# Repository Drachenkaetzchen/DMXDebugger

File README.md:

# DMX/RDM Adapter / RS485 Hub

This is a board which allows you to:
- Interconnect any standard DMX plugs, which includes XLR 3 pin male+female, XLR 5 pin male+female and RJ45
- Flip the data lines for each port in case of wiring error
- Connect each plug to an internal RS485 hub (in "direct" mode, each Data+/Data- lines are connected to each other)
- Terminate each port and enable/disable RX (only if port is connected to the RS485 hub)
- Connect a logic probe to the RS485 hub or to the secondary data ports (useful for the OLA logic sniffer)
- Display RX/TX status (RS485 hub mode only)
- Powered via battery (9V) or USB

# Applications

## Interconnect DMX plug formats directly

1. This mode works unpowered. You don't need to connect a battery or USB
2. Flip all switches from "TO HUB" to "DIRECT"
3. Connect exactly 2 plugs you wish to connect. If you connect more, data collisions can occur on the bus

## Interconnect DMX plug formats via the RS485 hub

1. This mode requires power. Connect a 9V battery or USB and flip the power switch to the specific "ON" position (either USB or BATTERY)
2. Flip the switches for all used ports from "DIRECT" to "HUB"
3. Connect as many plugs as you like
4. The LEDs should indicate RX/TX status

## Retrieve the data on the DMX bus via a logic analyzer

1. Set up as described in "Interconnect DMX plug formats via the RS485 hub"
2. Connect your logic probe to the GND and DATA pins on the bottom right

## Retrieve the data of the DMX secondary data lines

1. This mode works unpowered. However, you need an RS485 driver (like the SN75176) to convert the differential signal into logic levels
2. Connect your probe to the secondary data port

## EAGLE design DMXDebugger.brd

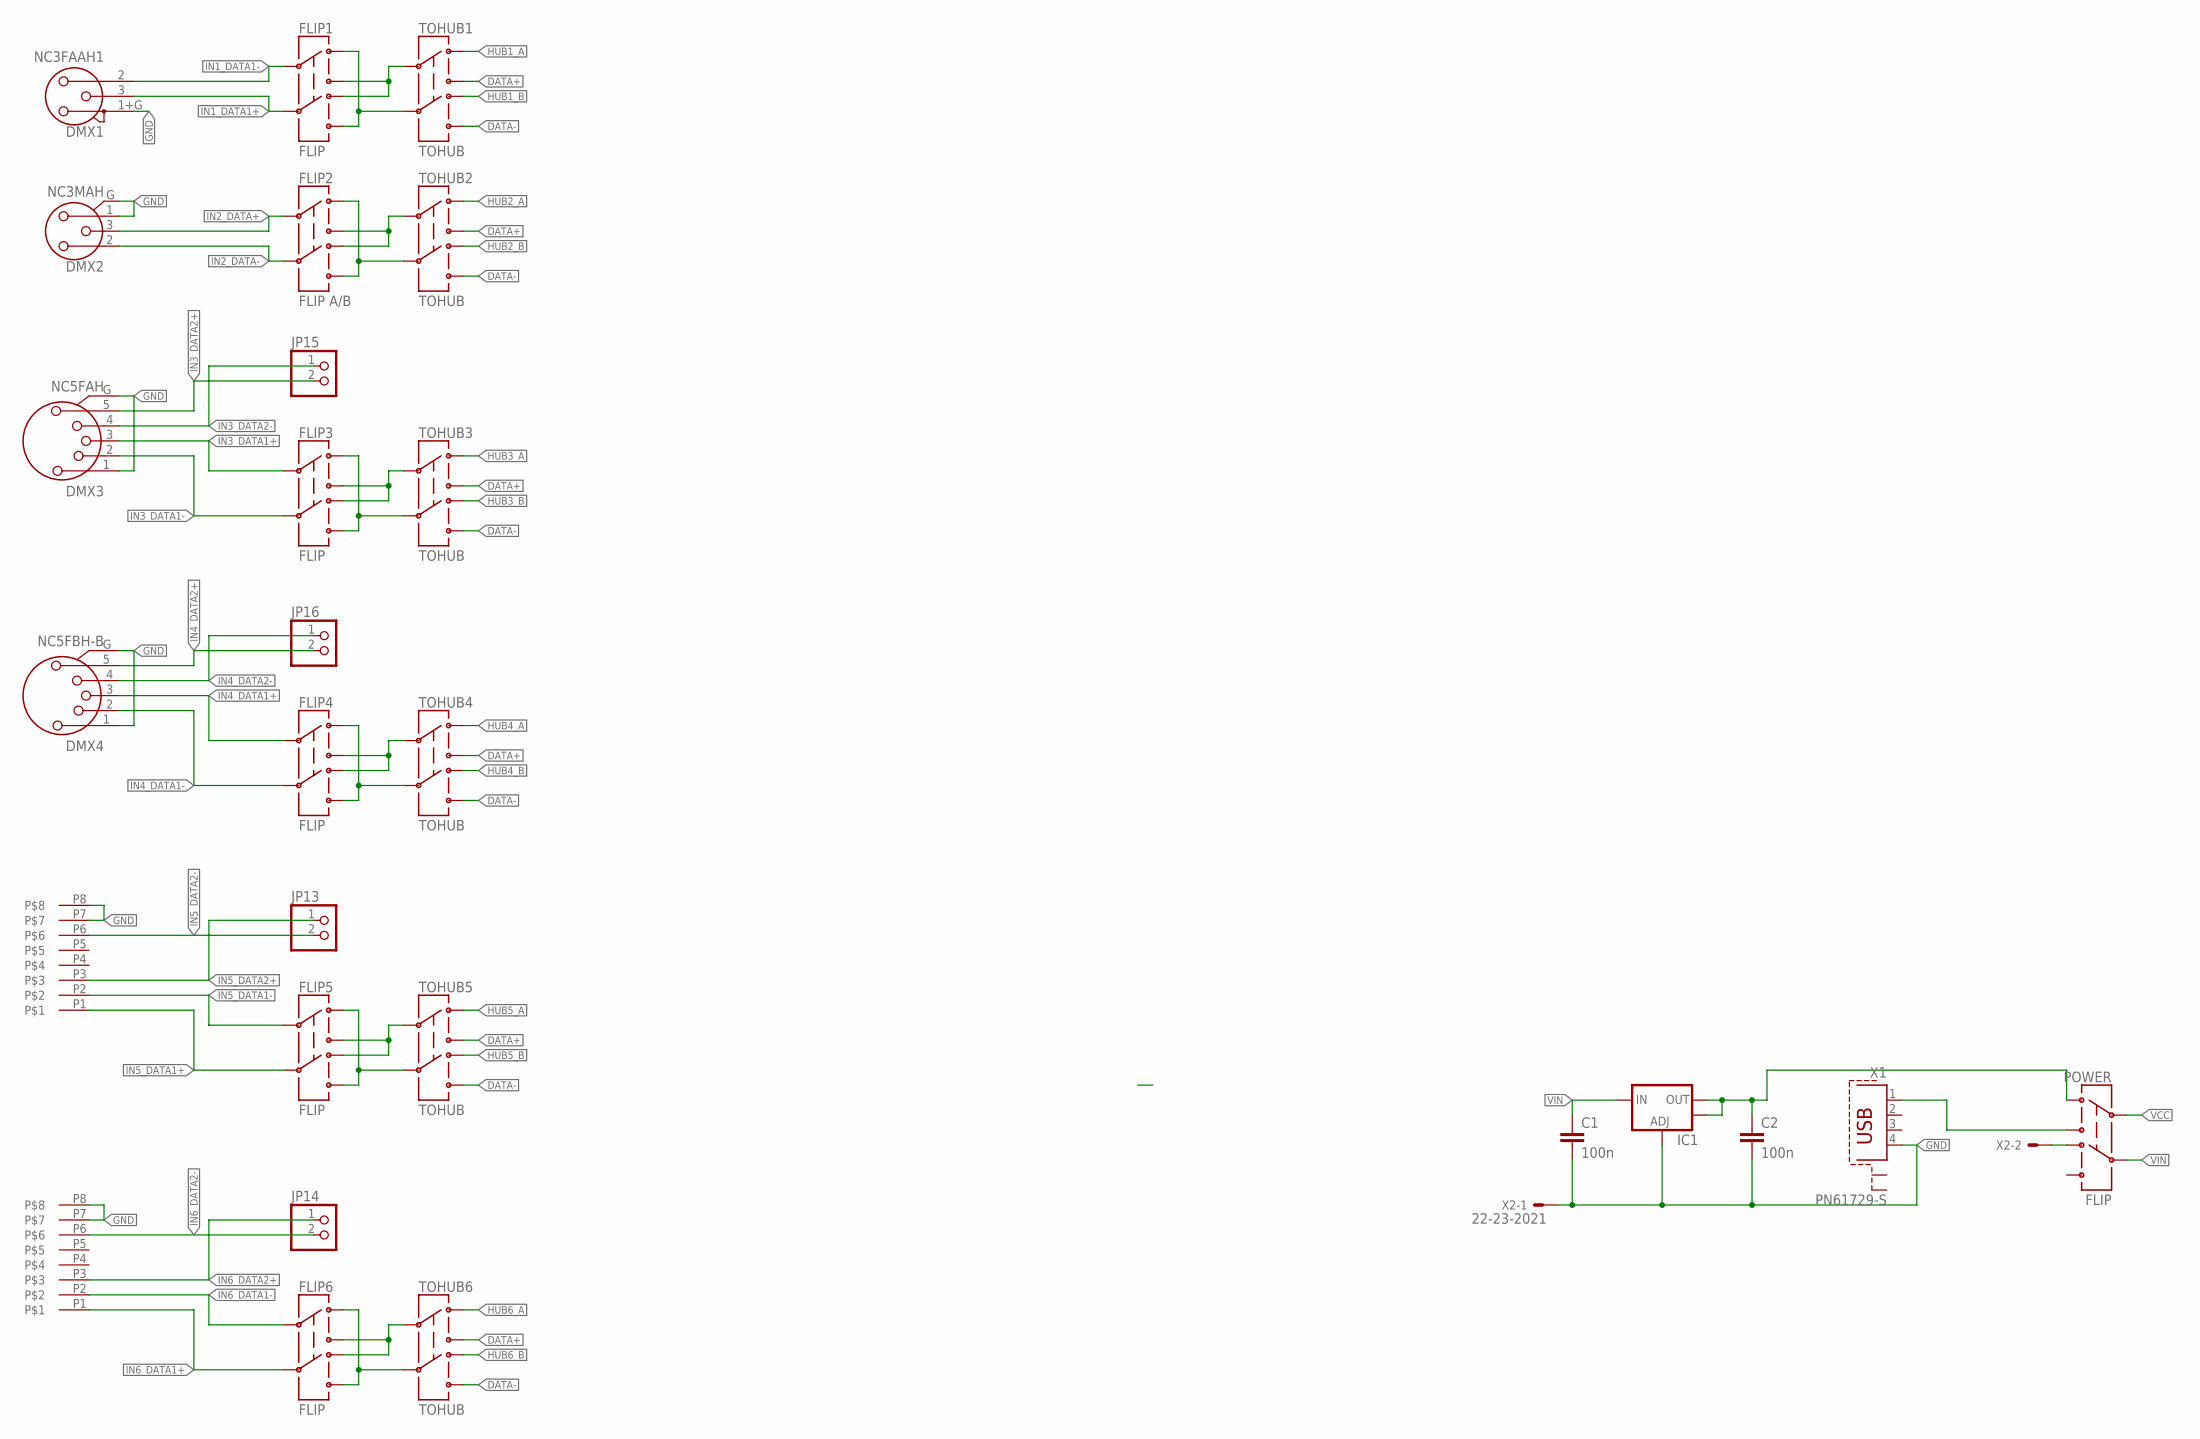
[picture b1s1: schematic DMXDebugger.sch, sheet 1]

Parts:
C1, C2: 100n; C1206
DMX1: NC3FAAH1; NC3FAH1
DMX2: NC3MAH; NC3FAH2
DMX3: NC5FAH
DMX4: NC5FBH-B
DMX5, DMX6: RJHS508; P-RJHS-538X
FLIP1, FLIP3, FLIP4, FLIP5, FLIP6: FLIP; MSS-2235
FLIP2: FLIP A/B; MSS-2235
IC1: V_REG_LM1117SOT223; SOT223
JP13, JP14, JP15, JP16: PINHD-1X2; 1X02
POWER: FLIP; MSS-2235
TOHUB1, TOHUB2, TOHUB3, TOHUB4, TOHUB5, TOHUB6: TOHUB; MSS-2235
X1: PN61729-S
X2: 22-23-2021

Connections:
DATA+: TOHUB1.3, TOHUB2.3, TOHUB3.3, TOHUB4.3, TOHUB5.3, TOHUB6.3
DATA-: TOHUB1.4 (6), TOHUB2.4 (6), TOHUB3.4 (6), TOHUB4.4 (6), TOHUB5.4 (6), TOHUB6.4 (6)
GND: C1.2, C2.2, DMX1.1+G (1), DMX2.1 (2), DMX2.G, DMX3.1, DMX3.G, DMX4.1, DMX4.G, DMX5.P7, DMX5.P8, DMX6.P7, DMX6.P8, IC1.1 (ADJ), X1.4, X2.1; also elsewhere on the board
HUB1_A: TOHUB1.1; also elsewhere on the board
HUB1_B: TOHUB1.6 (4); also elsewhere on the board
HUB2_A: TOHUB2.1; also elsewhere on the board
HUB2_B: TOHUB2.6 (4); also elsewhere on the board
HUB3_A: TOHUB3.1; also elsewhere on the board
HUB3_B: TOHUB3.6 (4); also elsewhere on the board
HUB4_A: TOHUB4.1; also elsewhere on the board
HUB4_B: TOHUB4.6 (4); also elsewhere on the board
HUB5_A: TOHUB5.1; also elsewhere on the board
HUB5_B: TOHUB5.6 (4); also elsewhere on the board
HUB6_A: TOHUB6.1; also elsewhere on the board
HUB6_B: TOHUB6.6 (4); also elsewhere on the board
IN1_DATA1+: DMX1.3, FLIP1.5
IN1_DATA1-: DMX1.2, FLIP1.2
IN2_DATA+: DMX2.3, FLIP2.2
IN2_DATA-: DMX2.2 (1), FLIP2.5
IN3_DATA1+: DMX3.3, FLIP3.2
IN3_DATA1-: DMX3.2, FLIP3.5
IN3_DATA2+: DMX3.5, JP15.2
IN3_DATA2-: DMX3.4, JP15.1
IN4_DATA1+: DMX4.3, FLIP4.2
IN4_DATA1-: DMX4.2, FLIP4.5
IN4_DATA2+: DMX4.5, JP16.2
IN4_DATA2-: DMX4.4, JP16.1
IN5_DATA1+: DMX5.P1, FLIP5.5
IN5_DATA1-: DMX5.P2, FLIP5.2
IN5_DATA2+: DMX5.P3, JP13.1
IN5_DATA2-: DMX5.P6, JP13.2
IN6_DATA1+: DMX6.P1, FLIP6.5
IN6_DATA1-: DMX6.P2, FLIP6.2
IN6_DATA2+: DMX6.P3, JP14.1
IN6_DATA2-: DMX6.P6, JP14.2
unnamed: POWER.6 (4), X2.2
unnamed: POWER.3, X1.1
unnamed: FLIP1.3, FLIP1.6 (4), TOHUB1.2
unnamed: FLIP1.1, FLIP1.4 (6), TOHUB1.5
unnamed: FLIP2.1, FLIP2.4 (6), TOHUB2.5
unnamed: FLIP2.3, FLIP2.6 (4), TOHUB2.2
unnamed: FLIP3.1, FLIP3.4 (6), TOHUB3.5
unnamed: FLIP4.1, FLIP4.4 (6), TOHUB4.5
unnamed: FLIP5.1, FLIP5.4 (6), TOHUB5.5
unnamed: FLIP3.3, FLIP3.6 (4), TOHUB3.2
unnamed: FLIP4.3, FLIP4.6 (4), TOHUB4.2
unnamed: FLIP5.3, FLIP5.6 (4), TOHUB5.2
unnamed: FLIP6.1, FLIP6.4 (6), TOHUB6.5
unnamed: FLIP6.3, FLIP6.6 (4), TOHUB6.2
VCC: POWER.2; also elsewhere on the board
VIN: C1.1, IC1.3 (IN), POWER.5
VOUT: C2.1, IC1.2 (OUT), IC1.4 (OUT), POWER.1

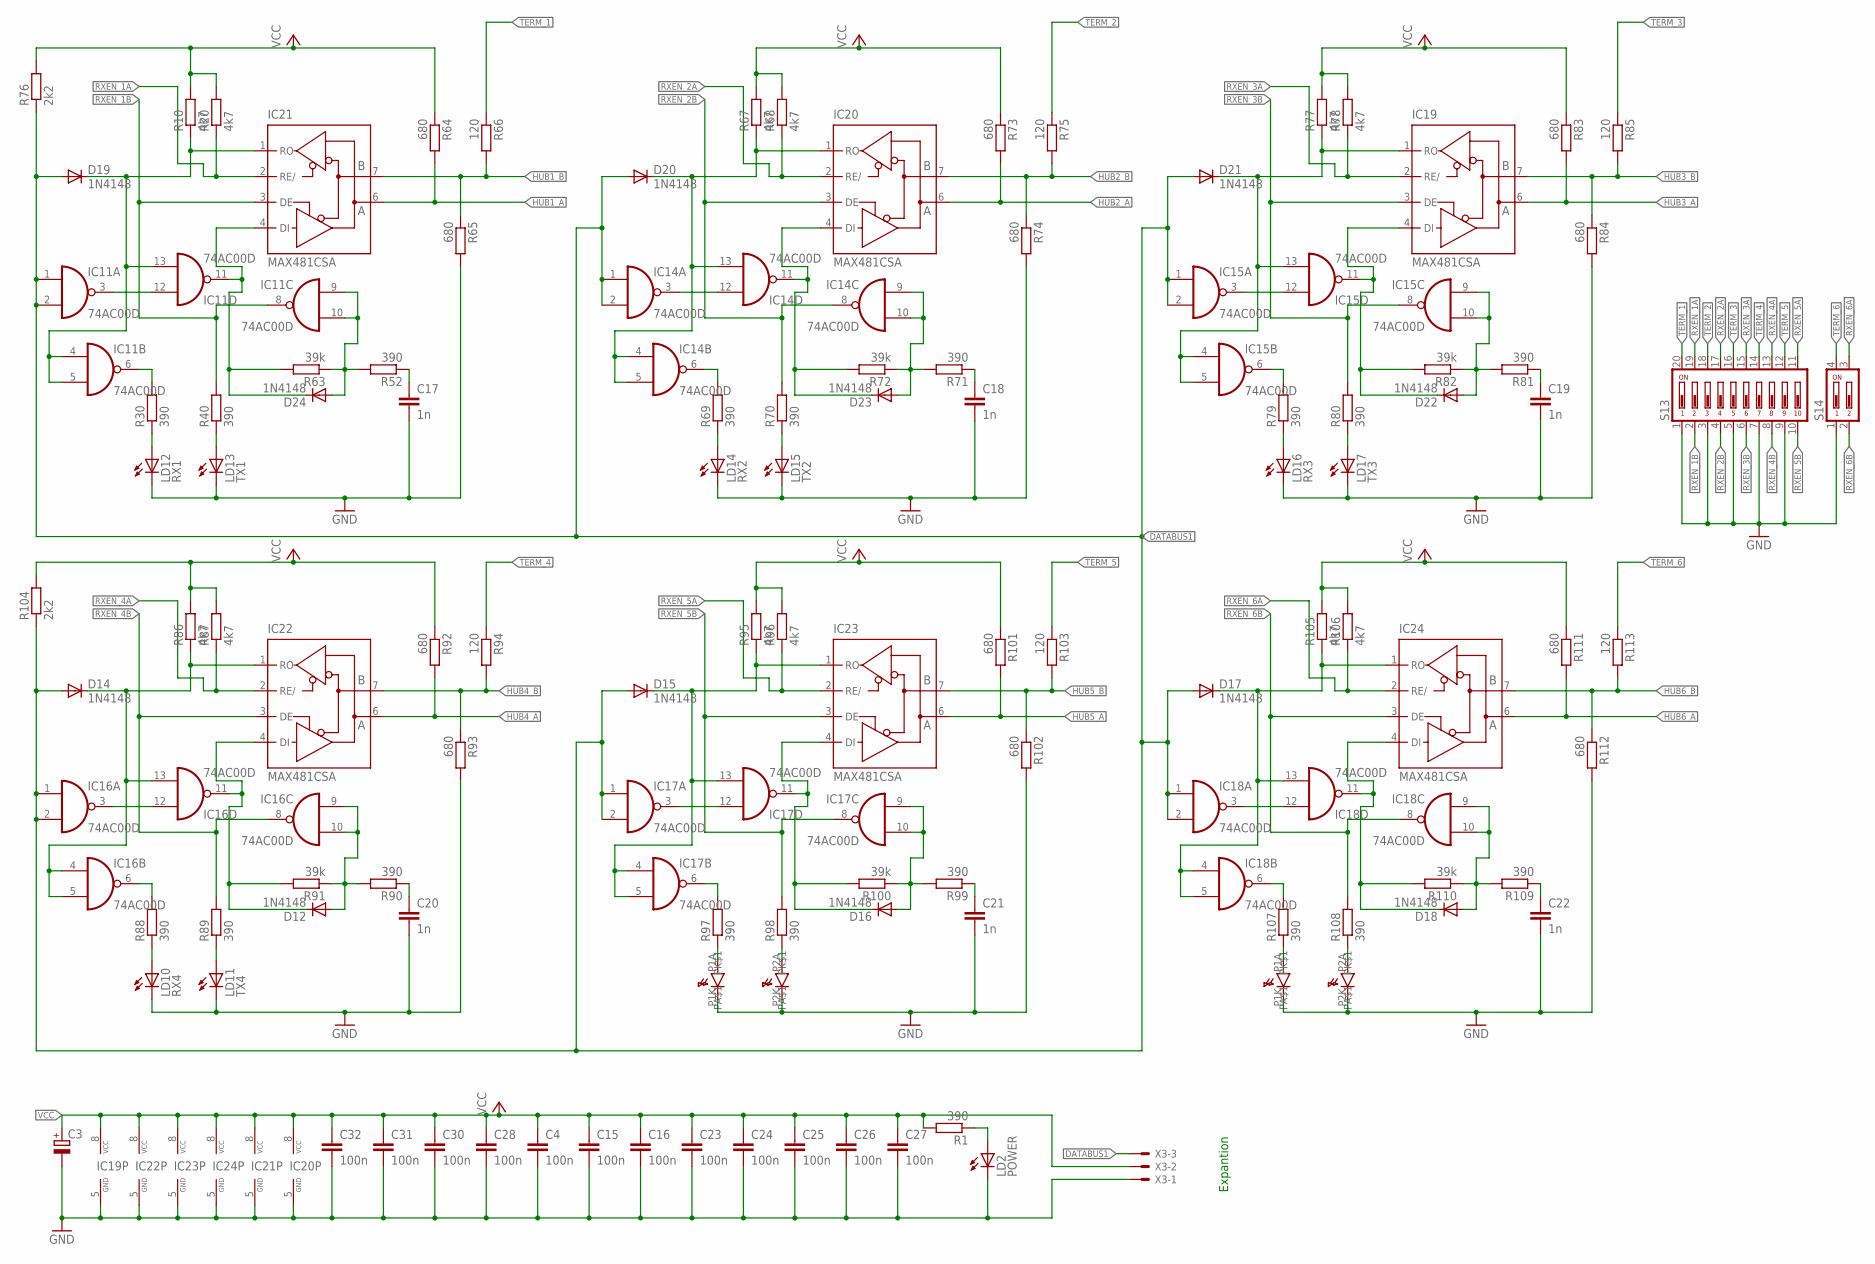
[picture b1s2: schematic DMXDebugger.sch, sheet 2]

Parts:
C3: CPOL-EUD; PANASONIC_D
C4, C15, C16, C23, C24, C25, C26, C27, C28, C30, C31, C32: 100n; C1206
C17, C18, C19, C20, C21, C22: 1n; C1206
D12, D14, D15, D16, D17, D18, D19, D20, D21, D22, D23, D24: 1N4148; MINIMELF
DMX5, DMX6: RJHS508; P-RJHS-538X
IC11, IC14, IC15, IC16, IC17, IC18: 74AC00D; SO14
IC19, IC20, IC21, IC22, IC23, IC24: MAX481CSA; SO08
LD2: POWER; CHIP-LED0603
LD10: RX4; CHIP-LED0603
LD11: TX4; CHIP-LED0603
LD12: RX1; CHIP-LED0603
LD13: TX1; CHIP-LED0603
LD14: RX2; CHIP-LED0603
LD15: TX2; CHIP-LED0603
LD16: RX3; CHIP-LED0603
LD17: TX3; CHIP-LED0603
R1, R30, R40, R52, R69, R70, R71, R79, R80, R81, R88, R89, R90, R97, R98, R99, R107, R108, R109: 390; R1206
R10, R20, R67, R68, R77, R78, R86, R87, R95, R96, R105, R106: 4k7; R1206
R63, R72, R82, R91, R100, R110: 39k; R1206
R64, R65, R73, R74, R83, R84, R92, R93, R101, R102, R111, R112: 680; R1206
R66, R75, R85, R94, R103, R113: 120; R1206
R76, R104: 2k2; R1206
S13: DIP10YL
S14: DIP02YL
X3: 22-23-2031

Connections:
DATABUS1: D14.A, D15.A, D17.A, D19.A, D20.A, D21.A, IC11.1 (I0), IC11.2 (I1), IC14.1 (I0), IC14.2 (I1), IC15.1 (I0), IC15.2 (I1), IC16.1 (I0), IC16.2 (I1), IC17.1 (I0), IC17.2 (I1), IC18.1 (I0), IC18.2 (I1), R76.1, R104.1, X3.3
GND: C3.-, C4.2, C15.2, C16.2, C17.2, C18.2, C19.2, C20.2, C21.2, C22.2, C23.2, C24.2, C25.2, C26.2, C27.2, C28.2, C30.2, C31.2, C32.2, DMX5.P1K (PK$1), DMX5.P2K (PK$1), DMX6.P1K (PK$1), DMX6.P2K (PK$1), IC11.7 (GND), IC14.7 (GND), IC15.7 (GND), IC16.7 (GND), IC17.7 (GND), IC18.7 (GND), IC19.5 (GND), IC20.5 (GND), IC21.5 (GND), IC22.5 (GND), IC23.5 (GND), IC24.5 (GND), LD2.C, LD10.C, LD11.C, LD12.C, LD13.C, LD14.C, LD15.C, LD16.C, LD17.C, R65.2, R74.2, R84.2, R93.2, R102.2, R112.2, S13.1, S13.3, S13.5, S13.7, S13.9, S14.1, X3.1; also elsewhere on the board
HUB1_A: IC21.6 (A), R64.2; also elsewhere on the board
HUB1_B: IC21.7 (B), R65.1, R66.2; also elsewhere on the board
HUB2_A: IC20.6 (A), R73.2; also elsewhere on the board
HUB2_B: IC20.7 (B), R74.1, R75.2; also elsewhere on the board
HUB3_A: IC19.6 (A), R83.2; also elsewhere on the board
HUB3_B: IC19.7 (B), R84.1, R85.2; also elsewhere on the board
HUB4_A: IC22.6 (A), R92.2; also elsewhere on the board
HUB4_B: IC22.7 (B), R93.1, R94.2; also elsewhere on the board
HUB5_A: IC23.6 (A), R101.2; also elsewhere on the board
HUB5_B: IC23.7 (B), R102.1, R103.2; also elsewhere on the board
HUB6_A: IC24.6 (A), R111.2; also elsewhere on the board
HUB6_B: IC24.7 (B), R112.1, R113.2; also elsewhere on the board
unnamed: LD2.A, R1.1
unnamed: LD13.A, R40.1
unnamed: LD12.A, R30.1
unnamed: D19.C, IC11.4 (I0), IC11.5 (I1), IC11.13 (I1), IC21.1 (RO), R10.1
unnamed: IC11.3 (O), IC11.12 (I0)
unnamed: IC11.6 (O), R30.2
unnamed: D24.A, IC11.9 (I0), IC11.10 (I1), R52.2, R63.1
unnamed: D24.C, IC11.11 (O), IC21.4 (DI), R63.2
unnamed: C17.1, R52.1
unnamed: LD15.A, R70.1
unnamed: LD14.A, R69.1
unnamed: D20.C, IC14.4 (I0), IC14.5 (I1), IC14.13 (I1), IC20.1 (RO), R67.1
unnamed: IC14.3 (O), IC14.12 (I0)
unnamed: IC14.6 (O), R69.2
unnamed: D23.A, IC14.9 (I0), IC14.10 (I1), R71.2, R72.1
unnamed: D23.C, IC14.11 (O), IC20.4 (DI), R72.2
unnamed: C18.1, R71.1
unnamed: LD17.A, R80.1
unnamed: LD16.A, R79.1
unnamed: D21.C, IC15.4 (I0), IC15.5 (I1), IC15.13 (I1), IC19.1 (RO), R77.1
unnamed: IC15.3 (O), IC15.12 (I0)
unnamed: IC15.6 (O), R79.2
unnamed: D22.A, IC15.9 (I0), IC15.10 (I1), R81.2, R82.1
unnamed: D22.C, IC15.11 (O), IC19.4 (DI), R82.2
unnamed: C19.1, R81.1
unnamed: LD11.A, R89.1
unnamed: LD10.A, R88.1
unnamed: D14.C, IC16.4 (I0), IC16.5 (I1), IC16.13 (I1), IC22.1 (RO), R86.1
unnamed: IC16.3 (O), IC16.12 (I0)
unnamed: IC16.6 (O), R88.2
unnamed: D12.A, IC16.9 (I0), IC16.10 (I1), R90.2, R91.1
unnamed: D12.C, IC16.11 (O), IC22.4 (DI), R91.2
unnamed: C20.1, R90.1
unnamed: DMX5.P2A (PA$1), R98.1
unnamed: DMX5.P1A (PA$1), R97.1
unnamed: D15.C, IC17.4 (I0), IC17.5 (I1), IC17.13 (I1), IC23.1 (RO), R95.1
unnamed: IC17.3 (O), IC17.12 (I0)
unnamed: IC17.6 (O), R97.2
unnamed: D16.A, IC17.9 (I0), IC17.10 (I1), R99.2, R100.1
unnamed: D16.C, IC17.11 (O), IC23.4 (DI), R100.2
unnamed: C21.1, R99.1
unnamed: DMX6.P2A (PA$1), R108.1
unnamed: DMX6.P1A (PA$1), R107.1
unnamed: D17.C, IC18.4 (I0), IC18.5 (I1), IC18.13 (I1), IC24.1 (RO), R105.1
unnamed: IC18.3 (O), IC18.12 (I0)
unnamed: IC18.6 (O), R107.2
unnamed: D18.A, IC18.9 (I0), IC18.10 (I1), R109.2, R110.1
unnamed: D18.C, IC18.11 (O), IC24.4 (DI), R110.2
unnamed: C22.1, R109.1
RXEN_1A: IC21.2 (RE/), R20.1, S13.19
RXEN_1B: IC11.8 (O), IC21.3 (DE), R40.2, S13.2
RXEN_2A: IC20.2 (RE/), R68.1, S13.17
RXEN_2B: IC14.8 (O), IC20.3 (DE), R70.2, S13.4
RXEN_3A: IC19.2 (RE/), R78.1, S13.15
RXEN_3B: IC15.8 (O), IC19.3 (DE), R80.2, S13.6
RXEN_4A: IC22.2 (RE/), R87.1, S13.13
RXEN_4B: IC16.8 (O), IC22.3 (DE), R89.2, S13.8
RXEN_5A: IC23.2 (RE/), R96.1, S13.11
RXEN_5B: IC17.8 (O), IC23.3 (DE), R98.2, S13.10
RXEN_6A: IC24.2 (RE/), R106.1, S14.3
RXEN_6B: IC18.8 (O), IC24.3 (DE), R108.2, S14.2
TERM_1: R66.1, S13.20
TERM_2: R75.1, S13.18
TERM_3: R85.1, S13.16
TERM_4: R94.1, S13.14
TERM_5: R103.1, S13.12
TERM_6: R113.1, S14.4
VCC: C3.+, C4.1, C15.1, C16.1, C23.1, C24.1, C25.1, C26.1, C27.1, C28.1, C30.1, C31.1, C32.1, IC11.14 (VCC), IC14.14 (VCC), IC15.14 (VCC), IC16.14 (VCC), IC17.14 (VCC), IC18.14 (VCC), IC19.8 (VCC), IC20.8 (VCC), IC21.8 (VCC), IC22.8 (VCC), IC23.8 (VCC), IC24.8 (VCC), R1.2, R10.2, R20.2, R64.1, R67.2, R68.2, R73.1, R76.2, R77.2, R78.2, R83.1, R86.2, R87.2, R92.1, R95.2, R96.2, R101.1, R104.2, R105.2, R106.2, R111.1, X3.2; also elsewhere on the board

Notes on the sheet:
Expantion

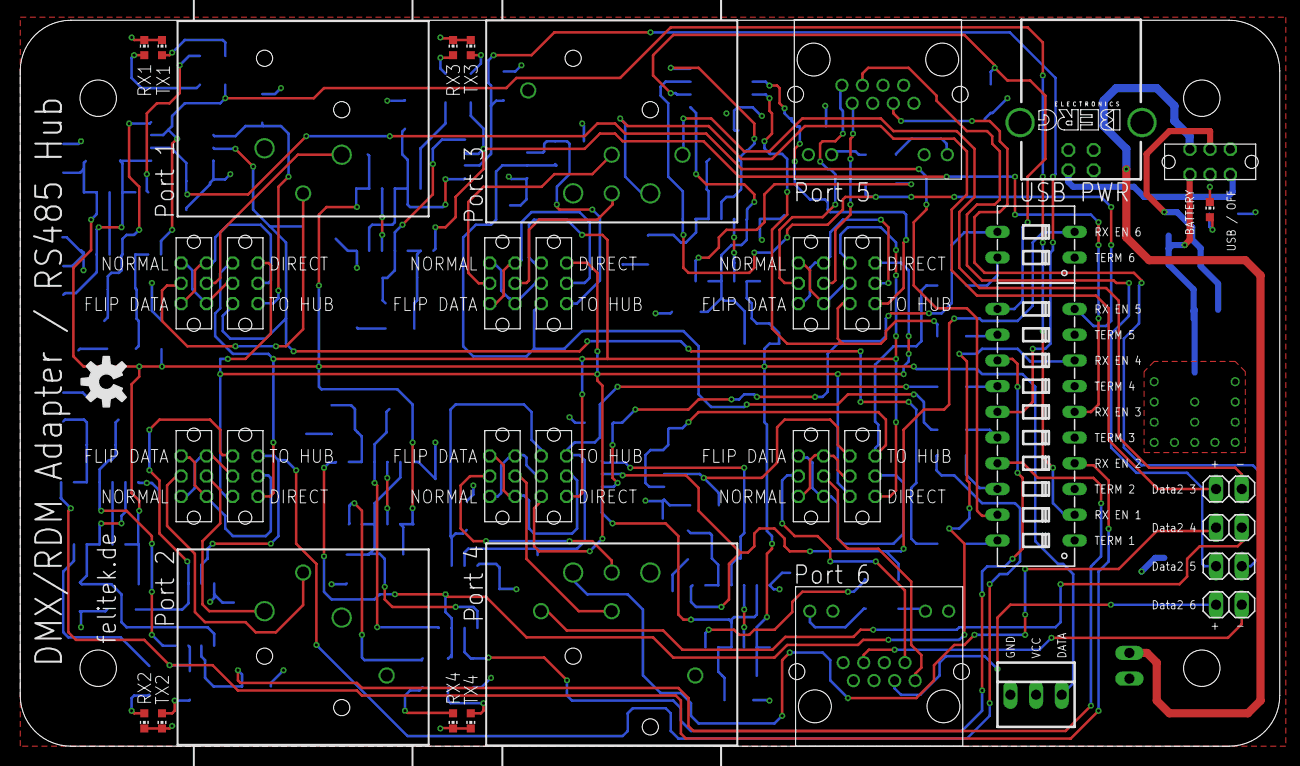
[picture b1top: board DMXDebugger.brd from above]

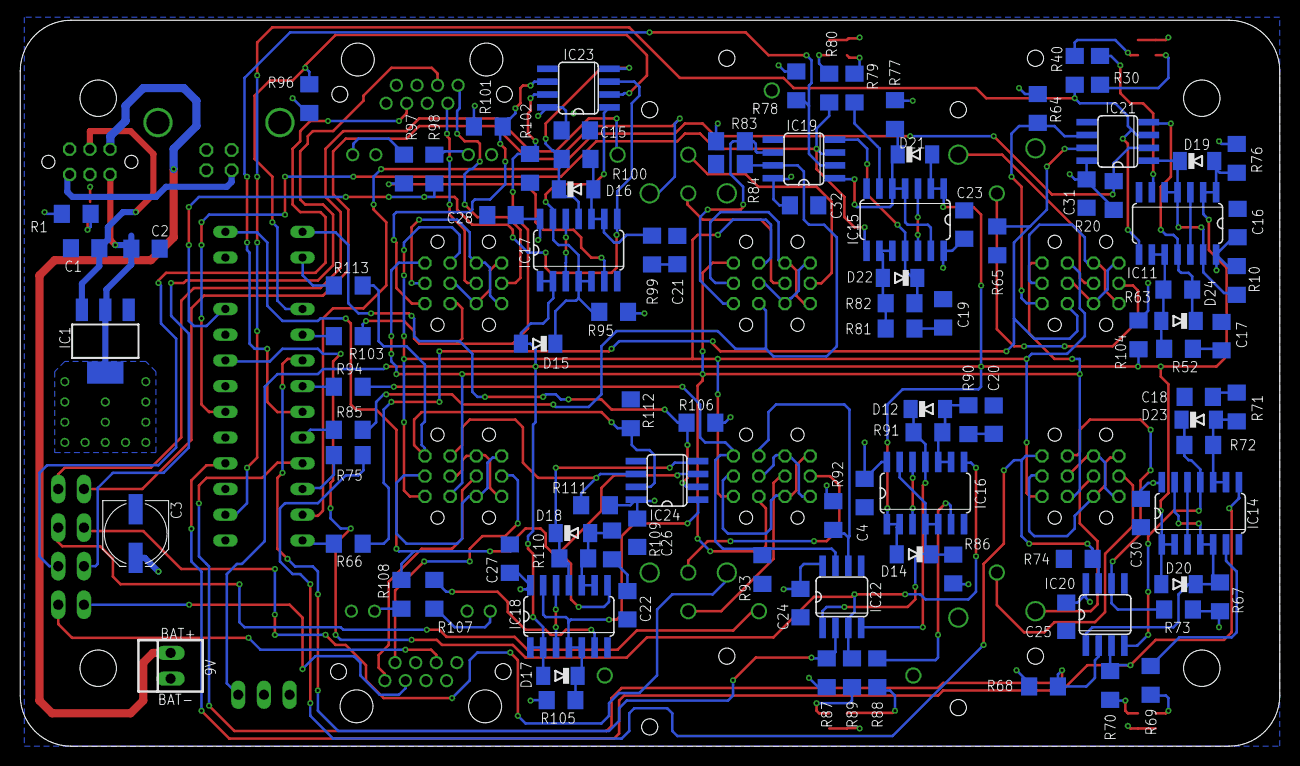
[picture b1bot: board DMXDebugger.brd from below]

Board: 2 copper layers, 124.4 x 71.7 mm, 141 parts (104 on the bottom side), 120 nets.

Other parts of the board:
U$1: OSHW-LOGO-M

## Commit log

2014-02-19 Moved LEDs from tValues to tNames
2014-02-19 Initial readme file
2014-02-19 Fixed forgotten unrouted trace (it was below a pad, so it wouldn't matter) Moved the felitek.de URL in line with the OSHW logo

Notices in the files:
parts and their libraries:
SparkFun: Licensing: CC v3.0 Share-Alike You are welcome to use this library for commercial purposes.
